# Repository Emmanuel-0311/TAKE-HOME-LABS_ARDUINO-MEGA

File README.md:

# Take-Home Labs: Laboratorios con Arduino Mega (ATmega2560)

## Introducción 🧠
Este repositorio contiene una serie de prácticas de laboratorio diseñadas para el autoaprendizaje y la experimentación en casa, enfocadas en la arquitectura del microcontrolador ATmega2560. Además, se empleó KiCad para el diseño de una shield personalizada, en la cual se integran tres plantas (electrónica, cinemática y de visualización) que permiten validar e implementar diferentes estrategias de control y adquisición de señales.

## Objetivo General 🎯
Desarrollar competencias en programación de sistemas embebidos utilizando la plataforma Arduino Mega, priorizando el control directo del hardware, así como la integración y validación de plantas físicas diseñadas en KiCad mediante una shield personalizada.

## Descipción de las plantas  🕹️
**Planta 1**: Planta electrónica basada en el CD4066, utilizada para la conmutación y enrutamiento de señales analógicas mediante interruptores controlados digitalmente. Integra redes RC en cascada que permiten modificar la dinámica del sistema, ajustando su respuesta según las etapas activadas.

**Planta 2:** Planta electromecánica basada en un motor DC N20 con encoder de cuadratura, donde la señal PWM controla la velocidad mediante un MOSFET.
El encoder proporciona retroalimentación de posición y velocidad, permitiendo implementar sistemas de control en lazo cerrado.

**Planta 3:** Planta electrónica basada en el LM3914N, utilizada para visualizar una señal analógica mediante una barra de LEDs proporcional al nivel de voltaje.
Incorpora un filtro pasa-bajas RC que suaviza la señal de entrada (PWM), permitiendo una lectura estable y continua en la visualización.

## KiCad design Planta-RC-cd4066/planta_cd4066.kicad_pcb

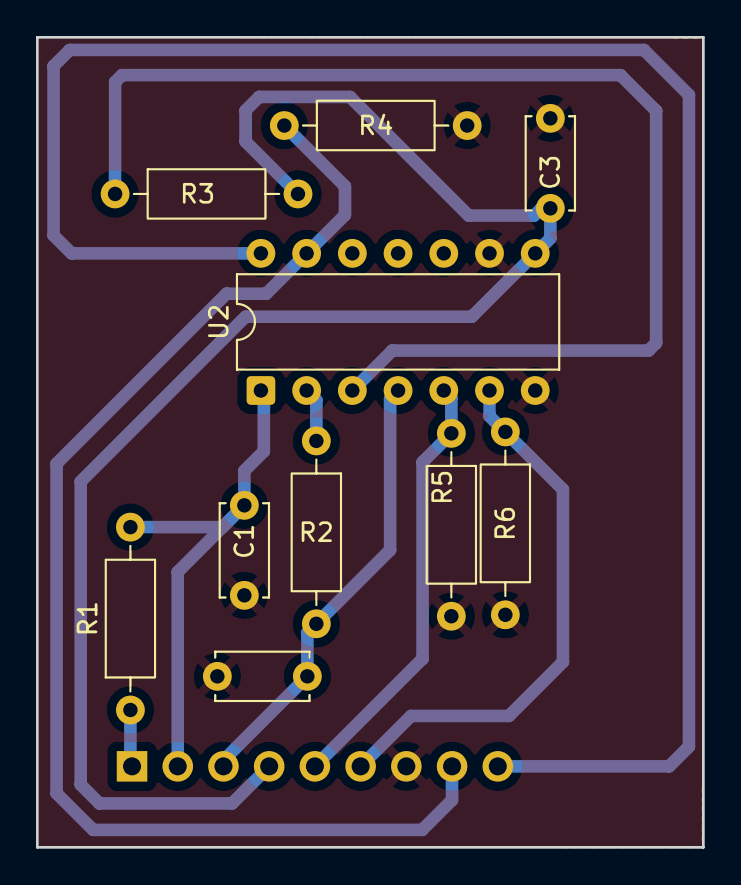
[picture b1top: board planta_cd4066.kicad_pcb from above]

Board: 2 copper layers, 37.0 x 45.0 mm, 11 parts (1 on the bottom side), 11 nets.

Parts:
C1, C2, C3: 1uF; C_Disc_D5.0mm_W2.5mm_P5.00mm
J1: Conn_01x09_Pin; PinHeader_1x09_P2.54mm_Vertical
R1, R2, R3: 1M; R_Axial_DIN0207_L6.3mm_D2.5mm_P10.16mm_Horizontal
R4, R5, R6: 10k; R_Axial_DIN0207_L6.3mm_D2.5mm_P10.16mm_Horizontal
U2: CD4066BE; DIP-14_W7.62mm

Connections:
GND: C1.2, C2.2, C3.2, J1.7, R4.2, R5.2, R6.2, U2.7 (V_{SS}), U2.9
unnamed: J1.1, R1.1
unnamed: C1.1, J1.2, R1.2, U2.1
unnamed: C2.1, J1.3, R2.2, U2.4
unnamed: C3.1, J1.4, R3.2, U2.8
unnamed: J1.5, R5.1, U2.5
unnamed: J1.6, R6.1, U2.6
unnamed: J1.8, R4.1, U2.13
unnamed: J1.9, U2.14 (V_{DD})
unnamed: R2.1, U2.2
unnamed: R3.1, U2.3

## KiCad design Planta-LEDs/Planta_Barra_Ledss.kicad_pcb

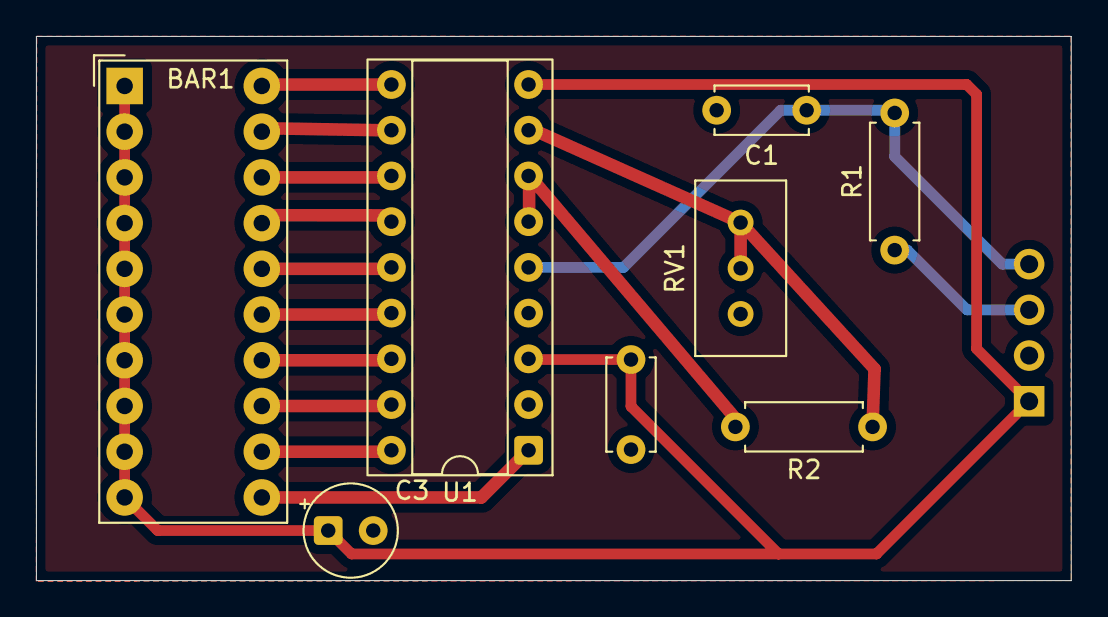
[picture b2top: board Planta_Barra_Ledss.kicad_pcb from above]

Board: 2 copper layers, 57.5 x 30.2 mm, 9 parts (1 on the bottom side), 16 nets.

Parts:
BAR1: HDSP-4830_2; HDSP-4830
C1: 10uF; C_Disc_D5.0mm_W2.5mm_P5.00mm
C2: 0.1uF; C_Disc_D5.0mm_W2.5mm_P5.00mm
C3: 2.2uF; CP_Radial_Tantal_D5.0mm_P2.50mm
J1: CONECTOR_SHIELD; PinHeader_1x04_P2.54mm_Vertical
R1: 4.7k; R_Axial_DIN0207_L6.3mm_D2.5mm_P7.62mm_Horizontal
R2: 1.2k; R_Axial_DIN0207_L6.3mm_D2.5mm_P7.62mm_Horizontal
RV1: 5k; Potentiometer_Bourns_3296W_Vertical
U1: LM3914N; DIP-18_W7.62mm_Socket

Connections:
/9V: BAR1.1 (A), BAR1.2 (A), BAR1.3 (A), BAR1.4 (A), BAR1.5 (A), BAR1.6 (A), BAR1.7 (A), BAR1.8 (A), BAR1.9 (A), BAR1.10 (A), C2.1, C3.1, J1.1, U1.3 (V+), U1.9 (MODE)
/ANALOG_FB: C1.1, J1.4, R1.2, U1.5 (SIG)
/LED1: BAR1.20 (K), U1.10 (LED10)
/LED2: BAR1.19 (K), U1.11 (LED9)
/LED3: BAR1.18 (K), U1.12 (LED8)
/LED4: BAR1.17 (K), U1.13 (LED7)
/LED5: BAR1.16 (K), U1.14 (LED6)
/LED6: BAR1.15 (K), U1.15 (LED5)
/LED7: BAR1.14 (K), U1.16 (LED4)
/LED8: BAR1.13 (K), U1.17 (LED3)
/LED9: BAR1.12 (K), U1.18 (LED2)
/LED10: BAR1.11 (K), U1.1 (LED1)
/PWM: J1.3, R1.1
GND: C1.2, C2.2, C3.2, J1.2, RV1.3, U1.2 (V-), U1.4 (RLO)
unnamed: R2.1, RV1.1, RV1.2, U1.8 (REFADJ)
unnamed: R2.2, U1.6 (RHI), U1.7 (REFOUT)

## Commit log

2026-04-24 Create Imagenes
2026-04-24 Create a
2026-04-24 Rename README.md to Materiales.md
